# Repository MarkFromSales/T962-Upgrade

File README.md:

# T962-Upgrade
My shot at replacing the electronics in the T962 with an ATMega328-based solution

Still untested, working through breadboard evaluation now

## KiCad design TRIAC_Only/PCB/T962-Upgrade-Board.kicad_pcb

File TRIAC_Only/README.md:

# T962-TRIAC
Reverse engineered TRIAC section of the T962

Built this as a replacement for the TRIAC controller section of the factory control board in the T962. Some of the upgrade and mod kits suggest cutting the original board but I want to leave it as a fall-back. I also want the option to have the heavier AC current on a separate board from the logic.

2019-03-18: Tested using the logic section of the [ES Technical upgrade kit](https://www.estechnical.co.uk/t962-reflow-oven-controller-complete-upgrade-package). I didn't run a complete cycle, only ran to 95 degrees and then cancelled. The fan and heating element worked as expected. The first run-through I had the SSR cables connected backwards.

For reference, here's the cabling for J1

```
MOC side
* Htr SSR -
* Htr SSR +
* Fan SSR -
* Fan SSR +
J1 indicator / screw side
```

[Picture of installed prototype](./TRIAC_working.png)

[CSV parts list from Digikey](./TRIAC_BOM.csv)

NOTE: I already had a box of 2.54mm connectors from Hilitchi on Amazon, ASIN B015Y6JOUG

This information is provided with no warranties expressed or implied

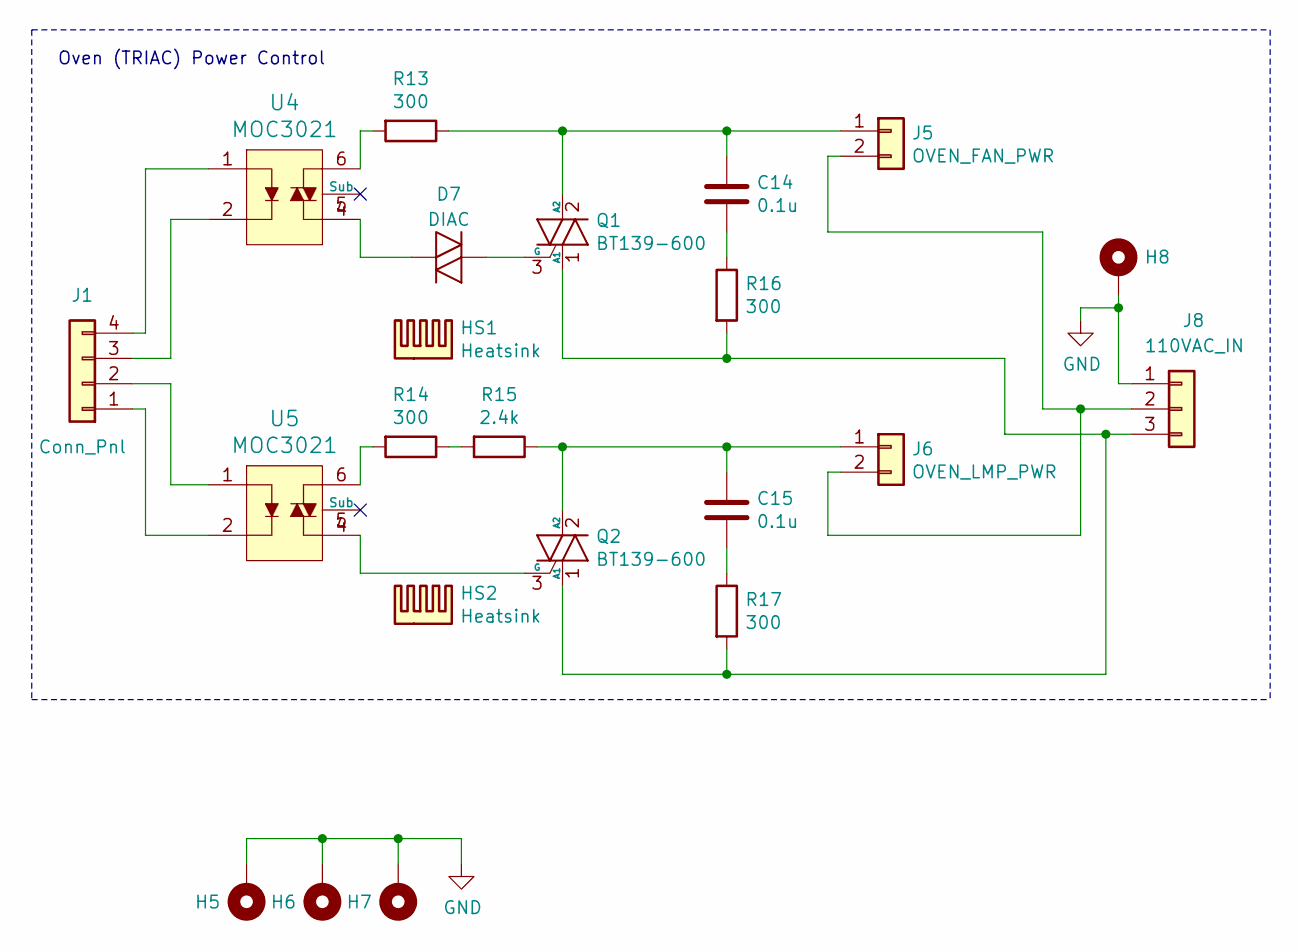
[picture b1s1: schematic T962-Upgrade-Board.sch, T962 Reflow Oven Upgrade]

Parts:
C14, C15: 0.1u; C_Rect_L13.0mm_W5.0mm_P10.00mm_FKS3_FKP3_MKS4
D7: DIAC; D_DO-34_SOD68_P7.62mm_Horizontal
H5, H6, H7, H8: MountingHole; MountingHole_3.7mm_Pad
HS1: Heatsink; Heatsink_TO-220_7-340-1PP-BA
HS2: Heatsink; Heatsink_TO-220_ATS-PCB1070
J1: Conn_Pnl; JST_XH_B04B-XH-A_1x04_P2.50mm_Vertical
J5: OVEN_FAN_PWR; JST_VH_B2P-VH-B_1x02_P3.96mm_Vertical
J6: OVEN_LMP_PWR; JST_VH_B2P-VH-B_1x02_P3.96mm_Vertical
J8: 110VAC_IN; JST_VH_B3P-VH-B_1x03_P3.96mm_Vertical
Q1, Q2: BT139-600; TO-220-3_Vertical
R13, R14, R16, R17: 300; R_2512_6332Metric_Pad1.52x3.35mm_HandSolder
R15: 2.4k; R_2512_6332Metric_Pad1.52x3.35mm_HandSolder
U4: MOC3021; SMDIP-6_W7.62mm; MPN MOC3021S-TA1; Digi-Key_PN 160-2045-1-ND
U5: MOC3021; SMDIP-6_W7.62mm; MPN MOC3021S-TA1

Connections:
GND: H5.1, H6.1, H7.1, H8.1, J8.1
unnamed: C14.1, J5.1, Q1.2 (A2), R13.1
unnamed: C14.2, R16.1
unnamed: C15.1, J6.1, Q2.2 (A2), R15.1
unnamed: C15.2, R17.1
unnamed: D7.1 (K), Q1.3 (G)
unnamed: D7.2 (A), U4.4
unnamed: J1.1, U5.2
unnamed: J1.2, U5.1
unnamed: J1.3, U4.2
unnamed: J1.4, U4.1
unnamed: J5.2, J6.2, J8.2
unnamed: J8.3, Q1.1 (A1), Q2.1 (A1), R16.2, R17.2
unnamed: Q2.3 (G), U5.4
unnamed: R13.2, U4.6
unnamed: R14.1, R15.2
unnamed: R14.2, U5.6

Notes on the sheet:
Oven (TRIAC) Power Control

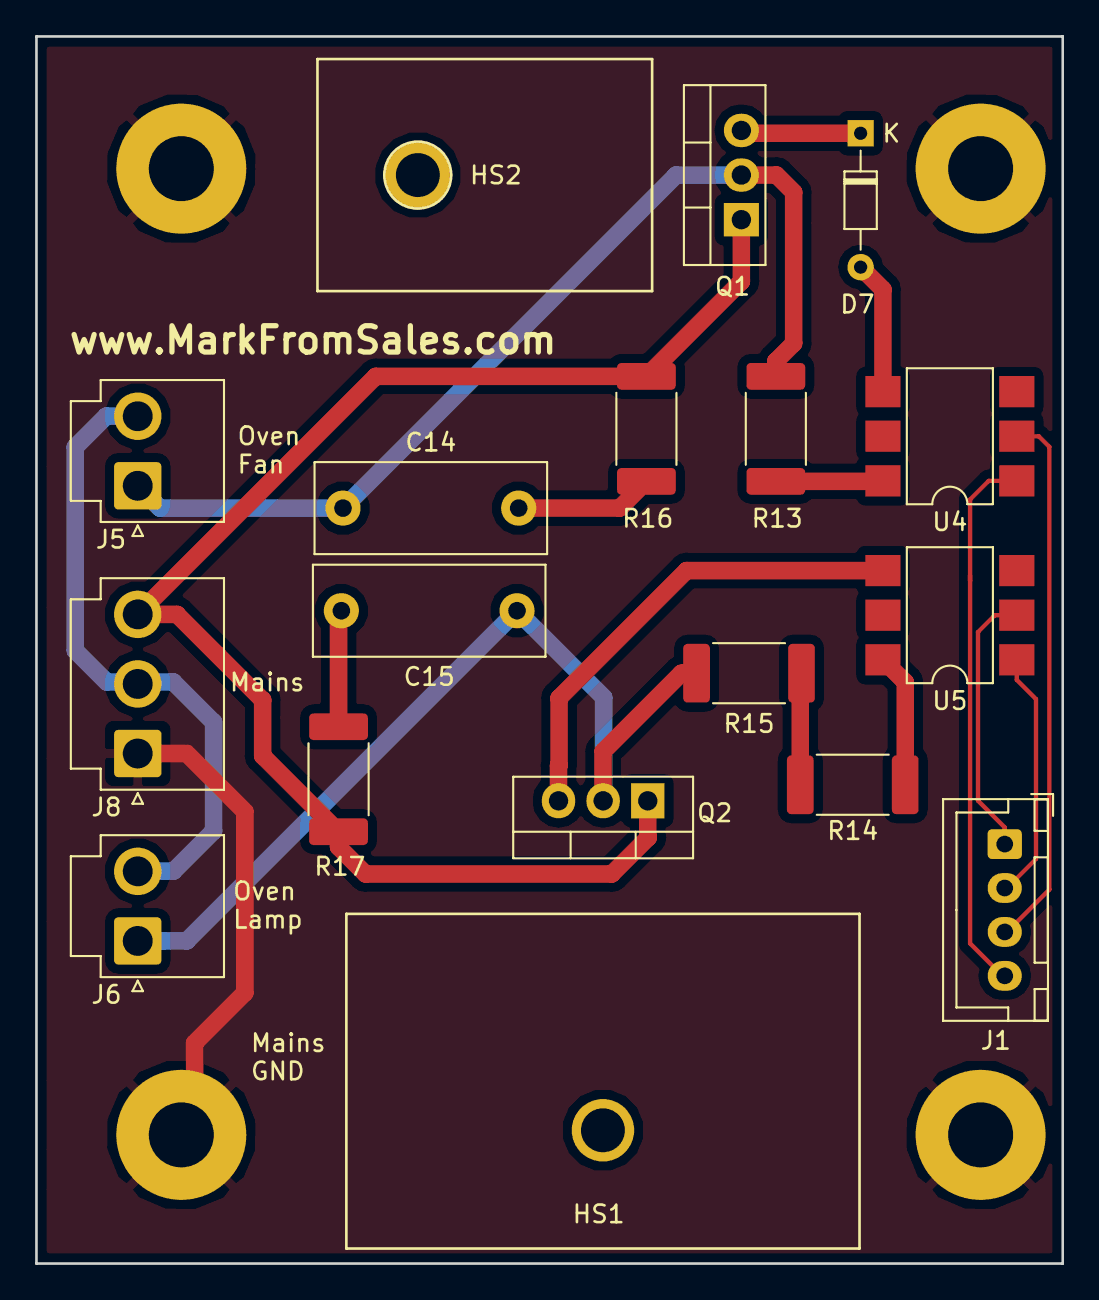
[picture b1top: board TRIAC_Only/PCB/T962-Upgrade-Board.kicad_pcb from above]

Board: 2 copper layers, 58.4 x 69.8 mm, 22 parts (0 on the bottom side), 17 nets.

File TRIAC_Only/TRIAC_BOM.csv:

Manufacturer Part Number,Manufacturer,Digi-Key Part Number,Customer Reference,Packaging,Part Status,Quantity,Unit Price,Extended Price,Description
MOC3021S-TA1,Lite-On Inc.,160-2045-1-ND,"U4, U5",Cut Tape (CT),Active,2,0.64,$1.28 ,OPTOISOLATOR 5KV TRIAC 6SMD
RMCF2512JT2K40,Stackpole Electronics Inc,RMCF2512JT2K40CT-ND,R15,Cut Tape (CT),Active,1,0.3,$0.30 ,RES 2.4K OHM 5% 1W 2512
RMCF2512FT300R,Stackpole Electronics Inc,RMCF2512FT300RCT-ND,"R13, R14, R16, R17",Cut Tape (CT),Active,4,0.38,$1.52 ,RES 300 OHM 1% 1W 2512
DB3,STMicroelectronics,497-3099-1-ND,D7,Cut Tape (CT),Active,1,0.4,$0.40 ,DIAC 28-36V 2A DO35
7-340-1PP-BA,CTS Thermal Management Products,294-1034-ND,HS1,Box,Active,1,2.69,$2.69 ,HEATSINK PWR VERT BLACK TO-220
"BT139-600E,127",WeEn Semiconductors,1740-1049-ND,"Q1, Q2",Tube,Active,2,0.87,$1.74 ,TRIAC SENS GATE 600V 16A TO220AB
577102B00000G,"Aavid, Thermal Division of Boyd Corporation",HS106-ND,HS2,Bag,Active,1,0.66,$0.66 ,"HEAT SINK TO-220 .375"" COMPACT"
B32641B0103J,EPCOS (TDK),495-7120-ND,C14,Bulk,Active,1,0.75,$0.75 ,CAP FILM 10000PF 5% 1KVDC RADIAL
104MKP275KD,Illinois Capacitor,1572-1007-ND,C15,Bulk,Active,1,0.53,$0.53 ,CAP FILM 0.1UF 10% 310VAC RADIAL

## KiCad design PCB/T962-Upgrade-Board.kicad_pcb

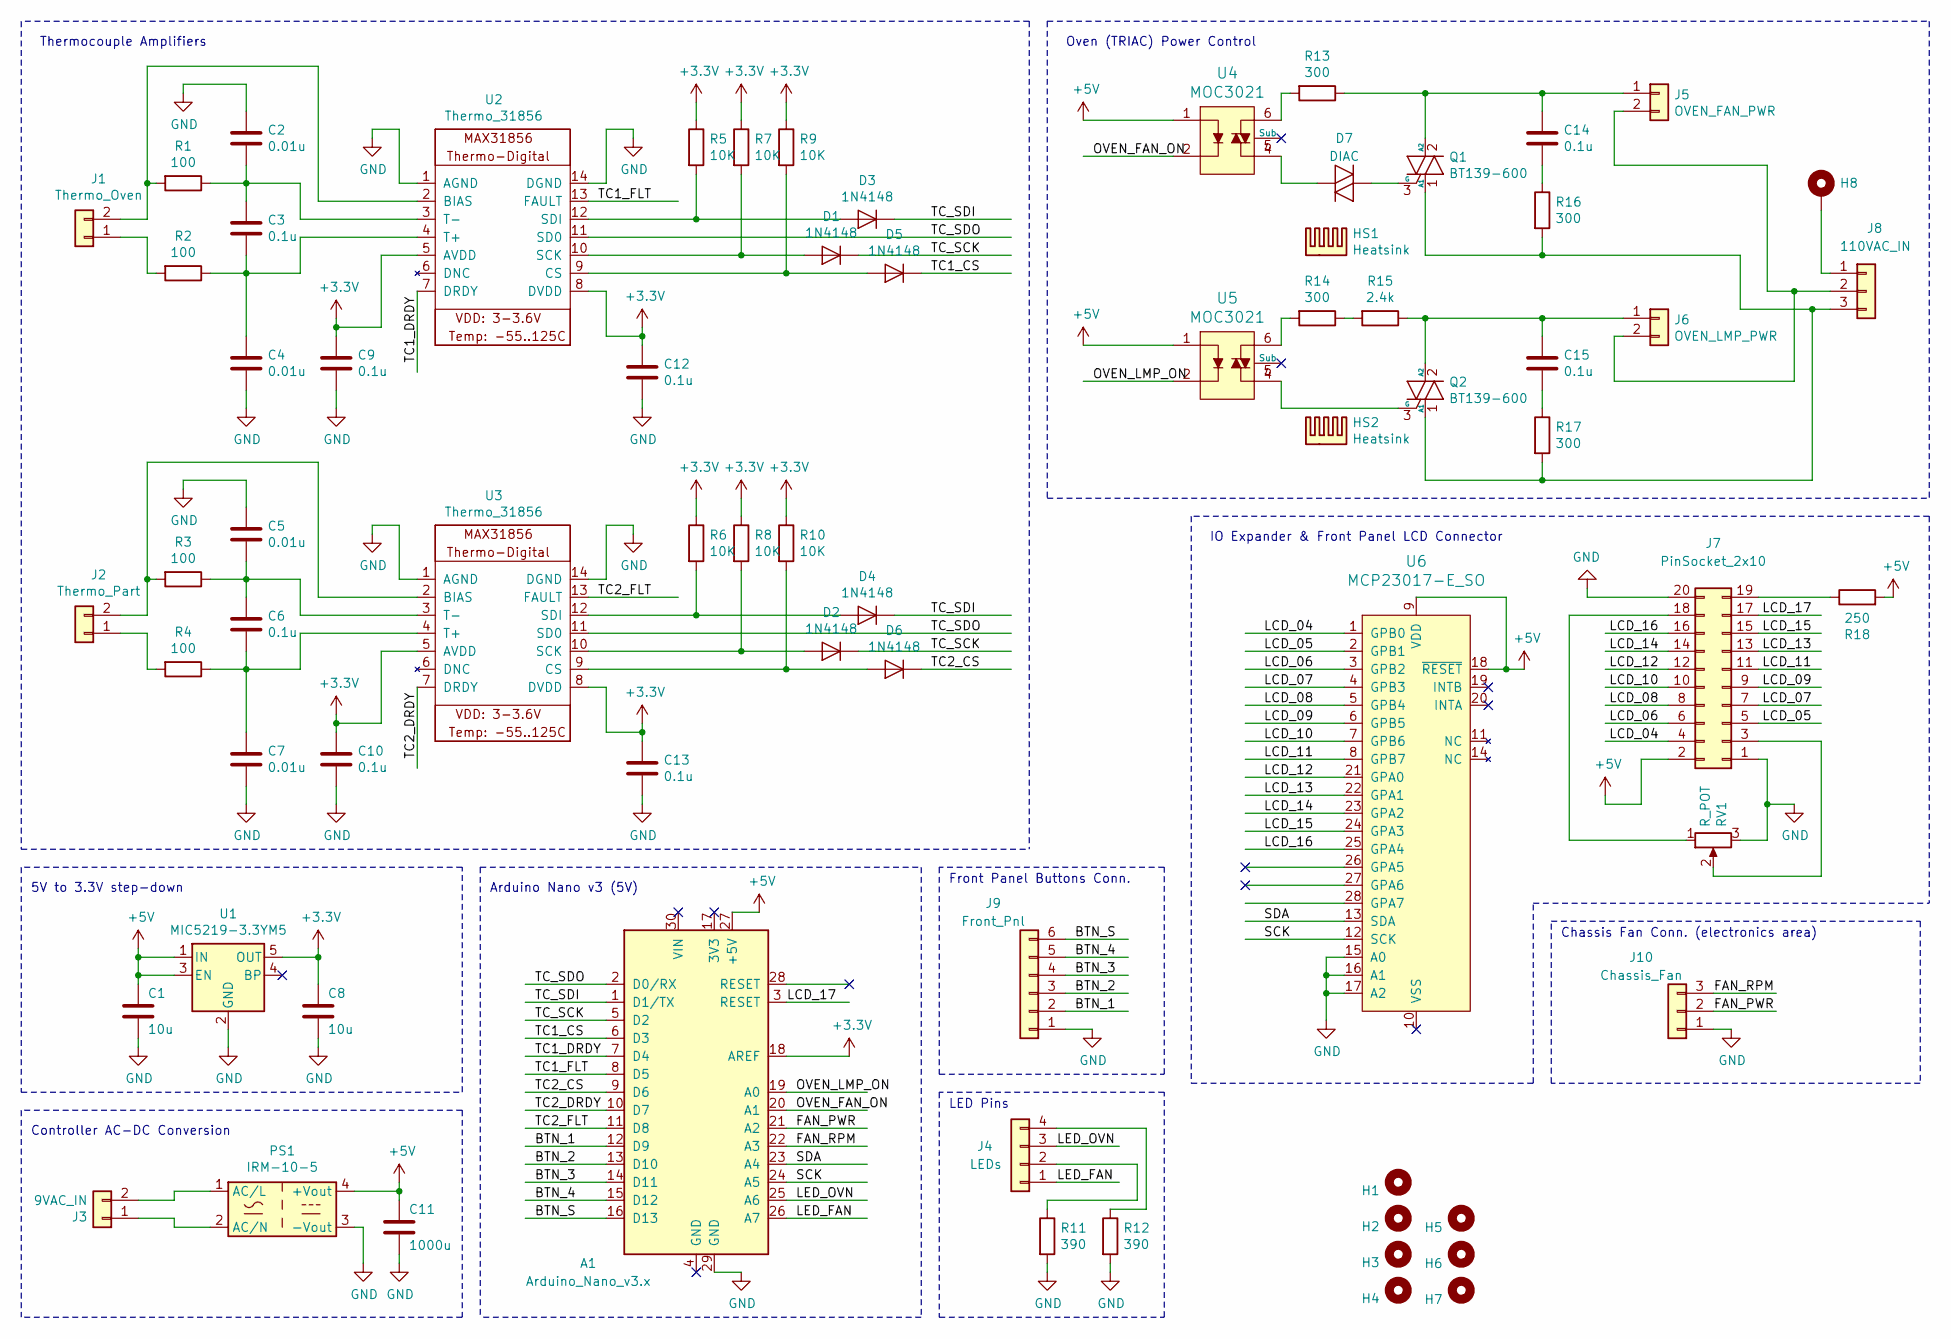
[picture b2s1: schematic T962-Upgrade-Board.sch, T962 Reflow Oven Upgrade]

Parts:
A1: Arduino_Nano_v3.x; Arduino_Nano
C1, C8: 10u; C_0805_2012Metric_Pad1.15x1.40mm_HandSolder
C2, C4, C5, C7: 0.01u; C_0805_2012Metric_Pad1.15x1.40mm_HandSolder
C3, C6, C9, C10, C12, C13: 0.1u; C_0805_2012Metric_Pad1.15x1.40mm_HandSolder
C11: 1000u; C_0805_2012Metric_Pad1.15x1.40mm_HandSolder
C14, C15: 0.1u; C_Rect_L13.0mm_W5.0mm_P10.00mm_FKS3_FKP3_MKS4
D1, D2, D3, D4, D5, D6: 1N4148; D_0805_2012Metric_Pad1.15x1.40mm_HandSolder
D7: DIAC; D_DO-34_SOD68_P7.62mm_Horizontal
H1, H2, H3, H4, H5, H6, H7: MountingHole; MountingHole_3.7mm
H8: MountingHole; MountingHole_3.7mm_Pad
HS1: Heatsink; Heatsink_TO-220_7-340-1PP-BA
HS2: Heatsink; Heatsink_TO-220_ATS-PCB1070
J1: Thermo_Oven; JST_VH_B2P-VH-B_1x02_P3.96mm_Vertical
J2: Thermo_Part; JST_VH_B2P-VH-B_1x02_P3.96mm_Vertical
J3: 9VAC_IN; TerminalBlock_Phoenix_MKDS-3-2-5.08_1x02_P5.08mm_Horizontal
J4: LEDs; JST_XH_B04B-XH-A_1x04_P2.50mm_Vertical
J5: OVEN_FAN_PWR; JST_VH_B2P-VH-B_1x02_P3.96mm_Vertical
J6: OVEN_LMP_PWR; JST_VH_B2P-VH-B_1x02_P3.96mm_Vertical
J7: PinSocket_2x10; PinSocket_2x10_P2.54mm_Vertical
J8: 110VAC_IN; JST_VH_B3P-VH-B_1x03_P3.96mm_Vertical
J9: Front_Pnl; PinHeader_1x06_P2.54mm_Vertical
J10: Chassis_Fan; JST_PH_B3B-PH-K_1x03_P2.00mm_Vertical
PS1: IRM-10-5; Converter_ACDC_MeanWell_IRM-10-xx_THT
Q1, Q2: BT139-600; TO-220-3_Vertical
R1, R2, R3, R4: 100; R_0805_2012Metric_Pad1.15x1.40mm_HandSolder
R5, R6, R7, R8, R9, R10: 10K; R_0805_2012Metric_Pad1.15x1.40mm_HandSolder
R11, R12: 390; R_0805_2012Metric_Pad1.15x1.40mm_HandSolder
R13, R14, R16, R17: 300; R_2512_6332Metric_Pad1.52x3.35mm_HandSolder
R15: 2.4k; R_2512_6332Metric_Pad1.52x3.35mm_HandSolder
R18: 250; R_0805_2012Metric_Pad1.15x1.40mm_HandSolder
RV1: R_POT; Potentiometer_Bourns_3314G_Vertical
U1: MIC5219-3.3YM5; SOT-23-5
U2, U3: Thermo_31856; TSSOP-14_4.4x5mm_P0.65mm
U4: MOC3021; SMDIP-6_W7.62mm; MPN MOC3021S-TA1; Digi-Key_PN 160-2045-1-ND
U5: MOC3021; SMDIP-6_W7.62mm; MPN MOC3021S-TA1
U6: MCP23017-E_SO; SOIC-28_W7.5mm; MPN MCP23017-E/SO; Digi-Key_PN MCP23017-E/SO-ND

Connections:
+3V3: A1.18 (AREF), C8.1, C9.1, C10.1, C12.1, C13.1, R5.1, R6.1, R7.1, R8.1, R9.1, R10.1, U1.5 (OUT), U2.5 (AVDD), U2.8 (DVDD), U3.5 (AVDD), U3.8 (DVDD)
+5V: A1.27 (+5V), C1.1, C11.1, J7.2, PS1.4 (+Vout), R18.2, U1.1 (IN), U1.3 (EN), U4.1, U5.1, U6.9 (VDD), U6.18 (~RESET)
/BTN_1: A1.12 (D9), J9.2
/BTN_2: A1.13 (D10), J9.3
/BTN_3: A1.14 (D11), J9.4
/BTN_4: A1.15 (D12), J9.5
/BTN_S: A1.16 (D13), J9.6
/FAN_PWR: A1.21 (A2), J10.2
/FAN_RPM: A1.22 (A3), J10.3
/LCD_04: J7.4, U6.1 (GPB0)
/LCD_05: J7.5, U6.2 (GPB1)
/LCD_06: J7.6, U6.3 (GPB2)
/LCD_07: J7.7, U6.4 (GPB3)
/LCD_08: J7.8, U6.5 (GPB4)
/LCD_09: J7.9, U6.6 (GPB5)
/LCD_10: J7.10, U6.7 (GPB6)
/LCD_11: J7.11, U6.8 (GPB7)
/LCD_12: J7.12, U6.21 (GPA0)
/LCD_13: J7.13, U6.22 (GPA1)
/LCD_14: J7.14, U6.23 (GPA2)
/LCD_15: J7.15, U6.24 (GPA3)
/LCD_16: J7.16, U6.25 (GPA4)
/LCD_17: A1.3 (RESET), J7.17
/LED_FAN: A1.26 (A7), J4.1
/LED_OVN: A1.25 (A6), J4.3
/OVEN_FAN_ON: A1.20 (A1), U4.2
/OVEN_LMP_ON: A1.19 (A0), U5.2
/SCK: A1.24 (A5), U6.12 (SCK)
/SDA: A1.23 (A4), U6.13 (SDA)
/TC1_CS: A1.6 (D3), D5.1 (K)
/TC1_DRDY: A1.7 (D4), U2.7 (DRDY)
/TC1_FLT: A1.8 (D5), U2.13 (FAULT)
/TC2_CS: A1.9 (D6), D6.1 (K)
/TC2_DRDY: A1.10 (D7), U3.7 (DRDY)
/TC2_FLT: A1.11 (D8), U3.13 (FAULT)
/TC_SCK: A1.5 (D2), D1.1 (K), D2.1 (K)
/TC_SDI: A1.1 (D1/TX), D3.1 (K), D4.1 (K)
/TC_SDO: A1.2 (D0/RX), U2.11 (SD0), U3.11 (SD0)
GND: A1.29 (GND), C1.2, C2.1, C4.2, C5.1, C7.2, C8.2, C9.2, C10.2, C11.2, C12.2, C13.2, J7.1, J7.20, J9.1, J10.1, PS1.3 (-Vout), R11.2, R12.2, RV1.3, U1.2 (GND), U2.1 (AGND), U2.14 (DGND), U3.1 (AGND), U3.14 (DGND), U6.15 (A0), U6.16 (A1), U6.17 (A2)
unnamed: C2.2, C3.1, R1.1, U2.3 (T-)
unnamed: C3.2, C4.1, R2.1, U2.4 (T+)
unnamed: C5.2, C6.1, R3.1, U3.3 (T-)
unnamed: C6.2, C7.1, R4.1, U3.4 (T+)
unnamed: C14.1, J5.1, Q1.2 (A2), R13.1
unnamed: C14.2, R16.1
unnamed: C15.1, J6.1, Q2.2 (A2), R15.1
unnamed: C15.2, R17.1
unnamed: D1.2 (A), R7.2, U2.10 (SCK)
unnamed: D2.2 (A), R8.2, U3.10 (SCK)
unnamed: D3.2 (A), R5.2, U2.12 (SDI)
unnamed: D4.2 (A), R6.2, U3.12 (SDI)
unnamed: D5.2 (A), R9.2, U2.9 (CS)
unnamed: D6.2 (A), R10.2, U3.9 (CS)
unnamed: D7.1 (K), Q1.3 (G)
unnamed: D7.2 (A), U4.4
unnamed: H8.1, J8.1
unnamed: J1.1, R2.2
unnamed: J1.2, R1.2, U2.2 (BIAS)
unnamed: J2.1, R4.2
unnamed: J2.2, R3.2, U3.2 (BIAS)
unnamed: J3.1, PS1.2 (AC/N)
unnamed: J3.2, PS1.1 (AC/L)
unnamed: J4.2, R11.1
unnamed: J4.4, R12.1
unnamed: J5.2, J6.2, J8.2
unnamed: J7.3, RV1.2
unnamed: J7.18, RV1.1
unnamed: J7.19, R18.1
unnamed: J8.3, Q1.1 (A1), Q2.1 (A1), R16.2, R17.2
unnamed: Q2.3 (G), U5.4
unnamed: R13.2, U4.6
unnamed: R14.1, R15.2
unnamed: R14.2, U5.6

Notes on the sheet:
Oven (TRIAC) Power Control
Controller AC-DC Conversion
5V to 3.3V step-down
Arduino Nano v3 (5V)
Thermocouple Amplifiers
IO Expander & Front Panel LCD Connector
LED Pins
Front Panel Buttons Conn.
Chassis Fan Conn. (electronics area)

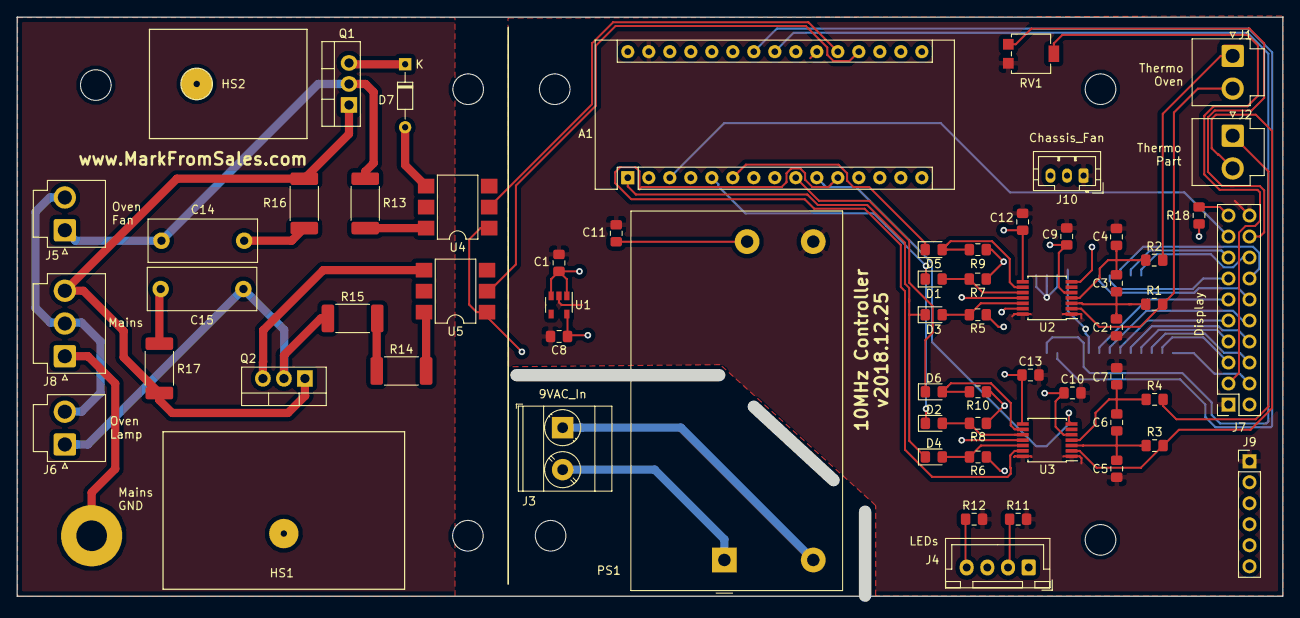
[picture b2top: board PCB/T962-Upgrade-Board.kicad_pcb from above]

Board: 4 copper layers, 151.7 x 69.3 mm, 71 parts (1 on the bottom side), 73 nets.

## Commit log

2019-02-02 Initial Upload
2019-02-13 Updated structure
